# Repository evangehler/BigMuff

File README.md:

# Big Muff Pi Build

This project serves as an example guitar pedal build and some best practices for documentation / builds for UF AES Design

*(I also just really wanted a Big Muff)*

## Overview

List out how to go about this jawn

## Table of Contents
- [Hardware](#hardware)
    - [Schematic](#schematic)
    - [PCB](#pcb)
- [Simulation](#ltspice-simulation)
- [Bill of Materials](#bill-of-materials-bom)

## Project Status

| Phase                 | Status         | 
| -----                 | --------       | 
| LTSpice Simulation    | ✅             | 
| Schematic             | ✅             | 
| Component Footprints  | ✅             | 
| PCB                   | ✅              | 

## Hardware 
### Schematic:

### PCB:

## LTSpice Simulation

## Bill of Materials (BOM)

| PART                      | QTY | Part #                                 |
| ------------------------- | --- | -------------------------------------- |
| BC549 NPN Transistor      | 4   | Q1, Q2, Q3, Q4                         |
| 1N4148 Silicon Diode      | 4   | D1, D2, D3, D4                         |
| 1N5817 Schottky Diode     | 1   | D6                                     |
| 5mm LED                   | 1   | D5                                     |
| 100k Potentiometer        | 3   | RV1, RV2, RV3                          |
| 470k Resistor             | 3   | R4, R8, R14                            |
| 430k Resistor             | 1   | R19                                    |
| 100k Resistor             | 3   | R10, R13, R20                          |
| 47k Resistor              | 1   | R2                                     |
| 33k Resistor              | 2   | R1, R17                                |
| 22k Resistor              | 1   | R18                                    |
| 15k Resistor              | 1   | R21                                    |
| 10k Resistor              | 5   | R5, R7, R9, R12, R15                   |
| 4.7k Resistor             | 1   | R23                                    |
| 3.3k Resistor             | 1   | R22                                    |
| 1k Resistor               | 1   | R6                                     |
| 150 Resistor              | 2   | R11, R16                               |
| 100 Resistor              | 1   | R3                                     |
| 100uF Electrolytic Cap    | 1   | C14                                    |
| 1uF Capacitor             | 4   | C1, C3, C6, C8                         |
| 100nF Capacitor           | 5   | C4, C7, C12, C13, C15                  |
| 10nF Capacitor            | 1   | C11                                    |
| 4nF Capacitor             | 1   | C10                                    |
| 470pF Capacitor           | 3   | C2, C5, C9                             |
| Neutrik NRJ4HF 1/4" Jack  | 2   | J1, J2                                 |
| Barrel Jack w/ Switch     | 1   | J4                                     |
| 2-Pin Header (2.54mm)     | 8   | J3, J5, J6, J7, J8, J9, J10, J11       |
| M3 Mounting Hole          | 4   | H1, H2, H3, H4                         |

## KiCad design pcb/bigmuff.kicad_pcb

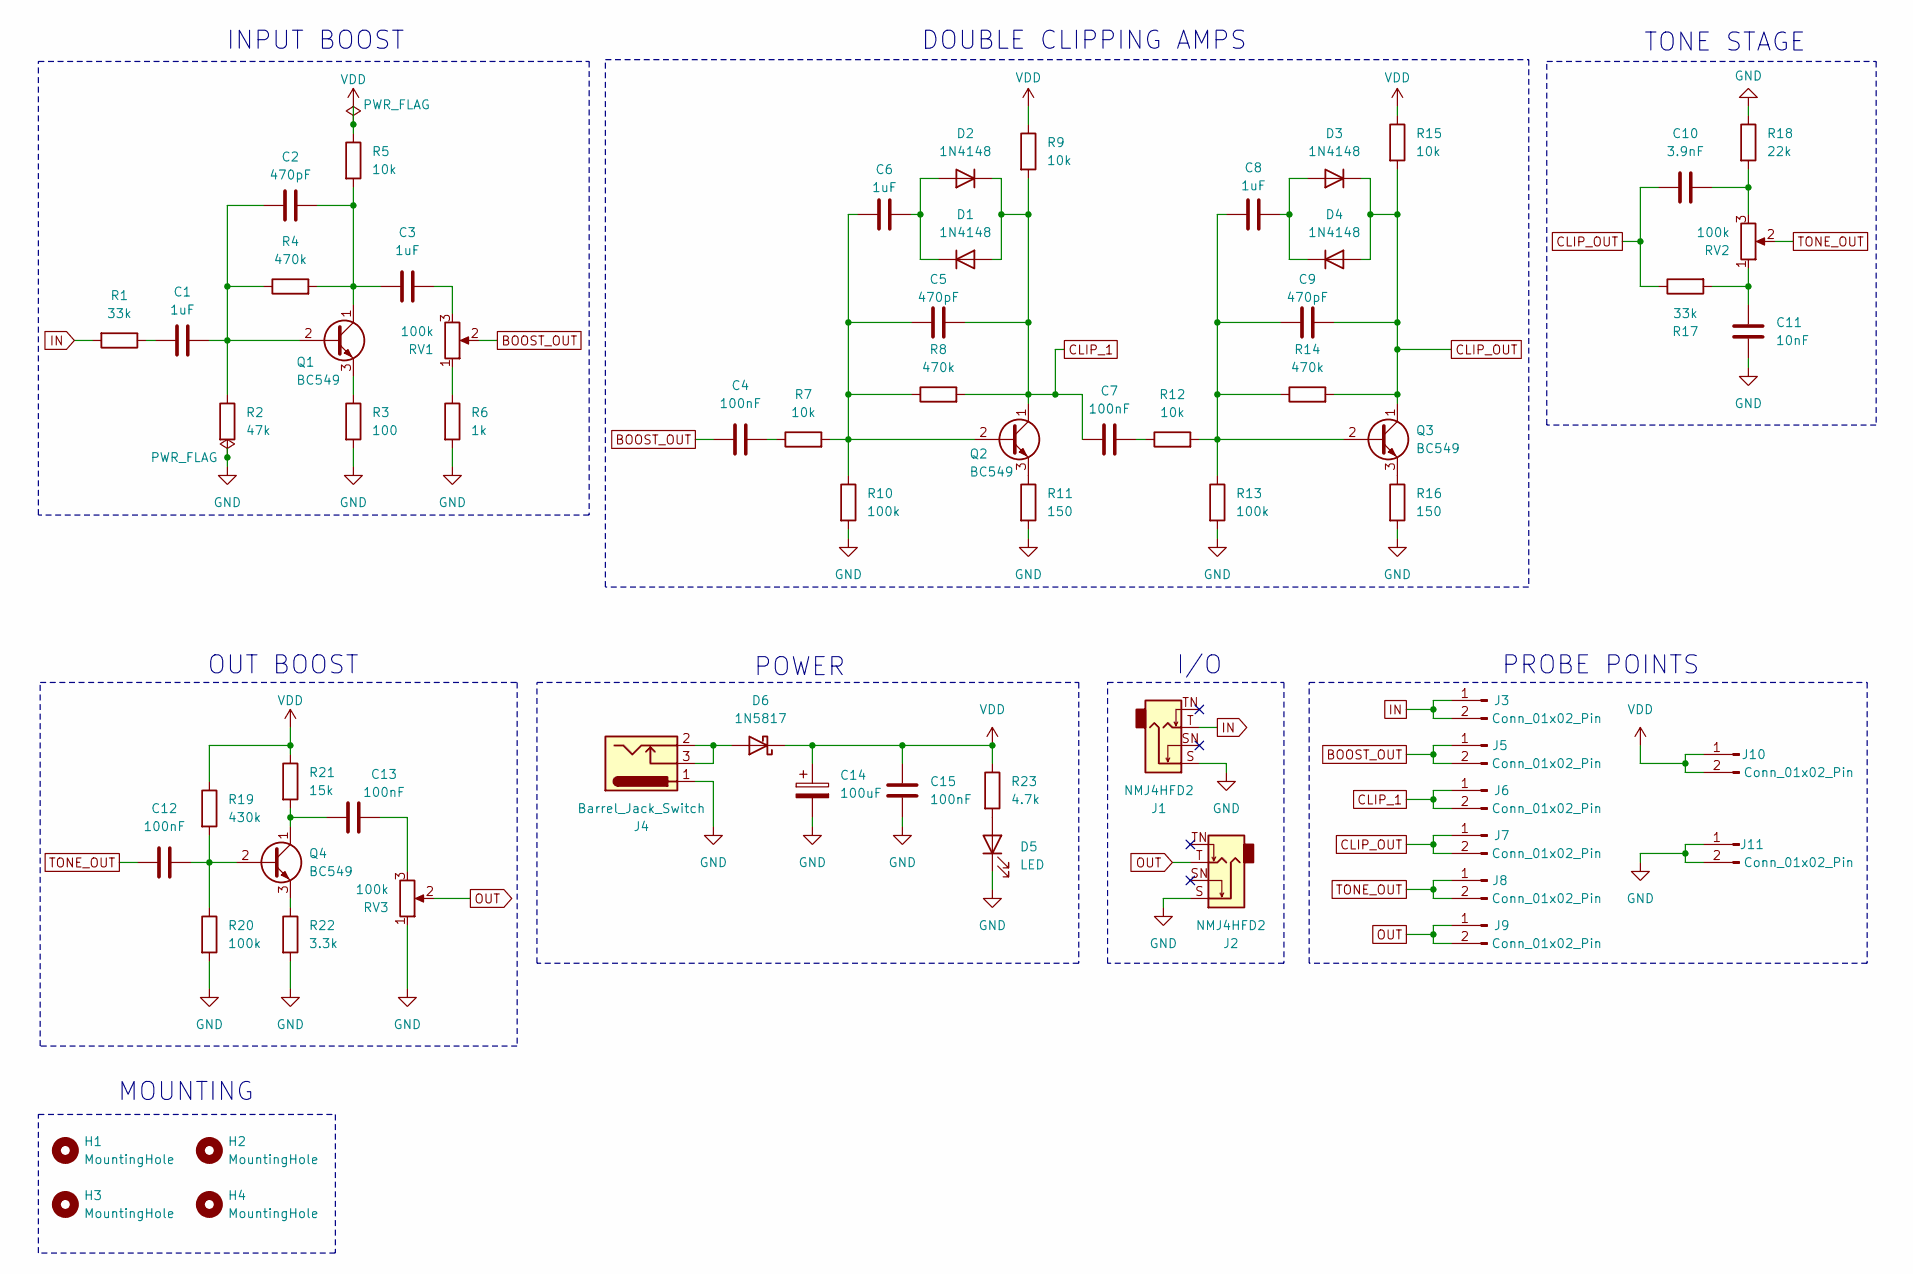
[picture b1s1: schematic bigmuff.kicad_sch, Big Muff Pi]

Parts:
C1, C3, C6, C8: 1uF; C_Rect_L7.2mm_W5.5mm_P5.00mm_FKS2_FKP2_MKS2_MKP2
C2, C5, C9: 470pF; C_Disc_D5.0mm_W2.5mm_P5.00mm
C4, C7, C12, C13: 100nF; C_Rect_L7.2mm_W2.5mm_P5.00mm_FKS2_FKP2_MKS2_MKP2
C10: 3.9nF; C_Disc_D5.0mm_W2.5mm_P5.00mm
C11: 10nF; C_Rect_L7.2mm_W2.5mm_P5.00mm_FKS2_FKP2_MKS2_MKP2
C14: 100uF; CP_Radial_D6.3mm_P2.50mm
C15: 100nF; C_Disc_D5.0mm_W2.5mm_P5.00mm
D1, D2, D3, D4: 1N4148; D_DO-35_SOD27_P7.62mm_Horizontal
D5: LED; LED_D5.0mm
D6: 1N5817; D_DO-41_SOD81_P10.16mm_Horizontal
H1, H2, H3, H4: MountingHole; MountingHole_3.2mm_M3
J1, J2: NMJ4HFD2; Jack_6.35mm_Neutrik_NMJ4HFD2_Horizontal
J3, J5, J6, J7, J8, J9, J10, J11: Conn_01x02_Pin; PinHeader_1x02_P2.54mm_Vertical
J4: Barrel_Jack_Switch; BarrelJack_Tayda_A-4118_Horizontal
Q1, Q2, Q3, Q4: BC549; TO-92_Inline_Wide
R1, R17: 33k; R_Axial_DIN0207_L6.3mm_D2.5mm_P10.16mm_Horizontal
R2: 47k; R_Axial_DIN0207_L6.3mm_D2.5mm_P10.16mm_Horizontal
R3: 100; R_Axial_DIN0207_L6.3mm_D2.5mm_P10.16mm_Horizontal
R4, R8, R14: 470k; R_Axial_DIN0207_L6.3mm_D2.5mm_P10.16mm_Horizontal
R5, R7, R9, R12, R15: 10k; R_Axial_DIN0207_L6.3mm_D2.5mm_P10.16mm_Horizontal
R6: 1k; R_Axial_DIN0207_L6.3mm_D2.5mm_P10.16mm_Horizontal
R10, R13, R20: 100k; R_Axial_DIN0207_L6.3mm_D2.5mm_P10.16mm_Horizontal
R11, R16: 150; R_Axial_DIN0207_L6.3mm_D2.5mm_P10.16mm_Horizontal
R18: 22k; R_Axial_DIN0207_L6.3mm_D2.5mm_P10.16mm_Horizontal
R19: 430k; R_Axial_DIN0207_L6.3mm_D2.5mm_P10.16mm_Horizontal
R21: 15k; R_Axial_DIN0207_L6.3mm_D2.5mm_P10.16mm_Horizontal
R22: 3.3k; R_Axial_DIN0207_L6.3mm_D2.5mm_P10.16mm_Horizontal
R23: 4.7k; R_Axial_DIN0207_L6.3mm_D2.5mm_P10.16mm_Horizontal
RV1, RV2, RV3: 100k; Potentiometer_Alpha_RD901F-40-00D_RoundLegs

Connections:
BOOST_OUT: C4.1, J5.1, J5.2, RV1.2
CLIP_1: C5.2, C7.1, D1.2 (A), D2.1 (K), J6.1, J6.2, Q2.1 (C), R8.2, R9.2
CLIP_OUT: C9.2, C10.1, D3.1 (K), D4.2 (A), J7.1, J7.2, Q3.1 (C), R14.2, R15.2, R17.1
GND: C11.1, C14.2, C15.2, D5.1 (K), J1.S, J2.S, J4.1, J11.1, J11.2, R2.2, R3.2, R6.2, R10.2, R11.2, R13.2, R16.2, R18.1, R20.2, R22.2, RV3.1
IN: J1.T, J3.1, J3.2, R1.2
unnamed: C1.2, R1.1
unnamed: C3.2, RV1.3
unnamed: C4.2, R7.1
unnamed: C7.2, R12.1
unnamed: C10.2, R18.2, RV2.3
unnamed: C11.2, R17.2, RV2.1
unnamed: C13.2, RV3.3
unnamed: C6.1, D1.1 (K), D2.2 (A)
unnamed: C8.1, D3.2 (A), D4.1 (K)
unnamed: D5.2 (A), R23.2
unnamed: D6.2 (A), J4.2, J4.3
unnamed: C1.1, C2.1, Q1.2 (B), R2.1, R4.1
unnamed: C2.2, C3.1, Q1.1 (C), R4.2, R5.2
unnamed: Q1.3 (E), R3.1
unnamed: C5.1, C6.2, Q2.2 (B), R7.2, R8.1, R10.1
unnamed: Q2.3 (E), R11.1
unnamed: C8.2, C9.1, Q3.2 (B), R12.2, R13.1, R14.1
unnamed: Q3.3 (E), R16.1
unnamed: C12.2, Q4.2 (B), R19.2, R20.1
unnamed: C13.1, Q4.1 (C), R21.2
unnamed: Q4.3 (E), R22.1
unnamed: R6.1, RV1.1
OUT: J2.T, J9.1, J9.2, RV3.2
TONE_OUT: C12.1, J8.1, J8.2, RV2.2
VDD: C14.1, C15.1, D6.1 (K), J10.1, J10.2, R5.1, R9.1, R15.1, R19.1, R21.1, R23.1

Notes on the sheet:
OUT BOOST
DOUBLE CLIPPING AMPS
I/O
PROBE POINTS
POWER
INPUT BOOST
TONE STAGE
MOUNTING

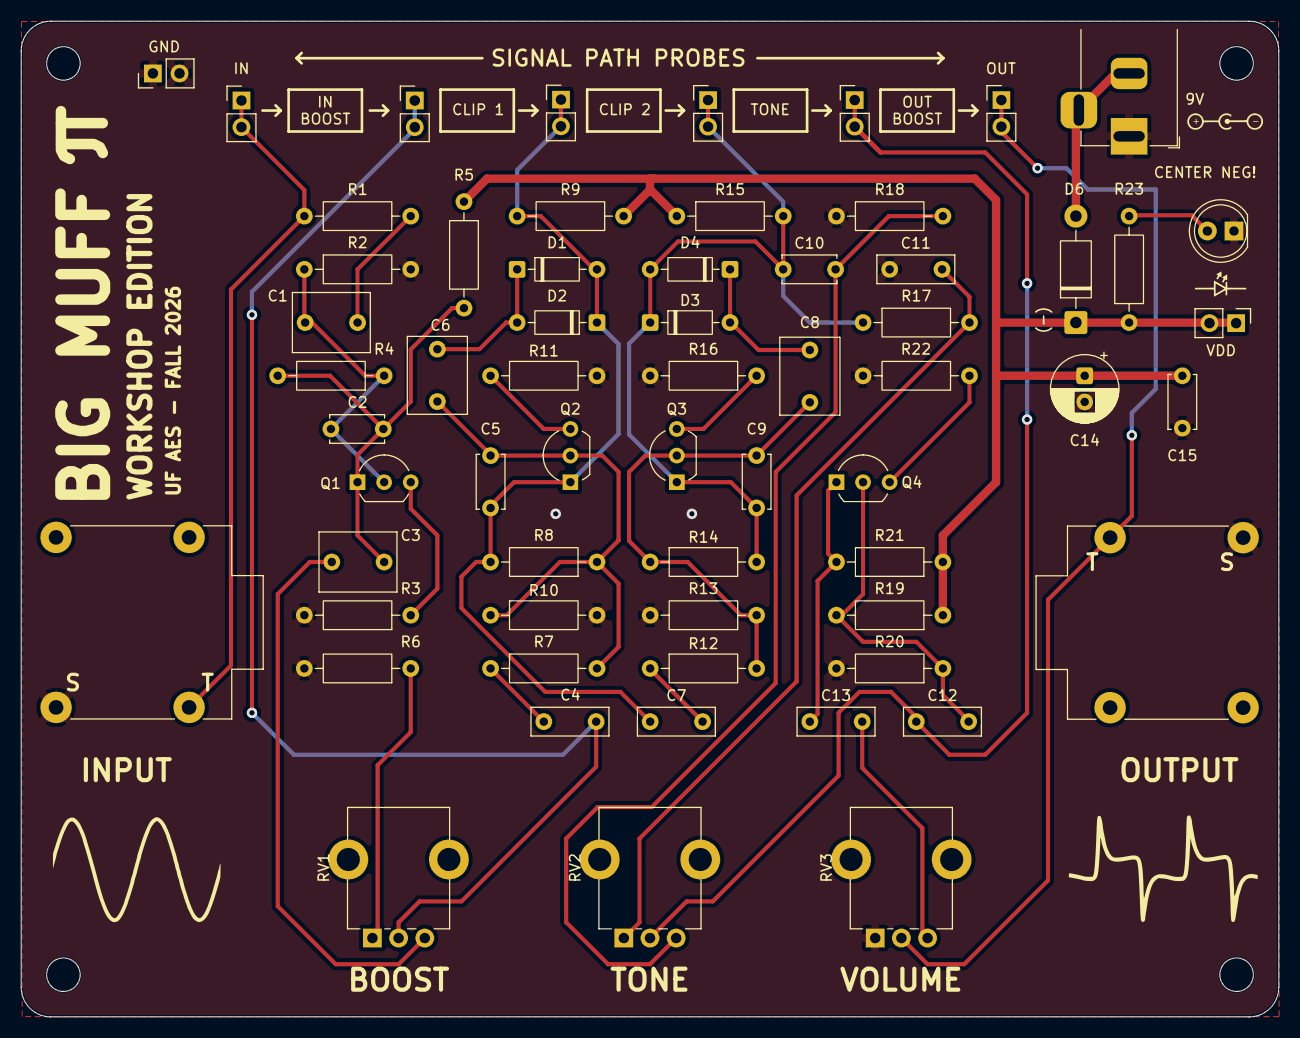
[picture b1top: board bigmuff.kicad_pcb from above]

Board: 2 copper layers, 120.1 x 95.1 mm, 66 parts (0 on the bottom side), 30 nets.

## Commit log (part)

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2026-02-05 Added LTSpice sim
2026-02-05 Added README
2026-02-05 Added .gitignore
2026-02-05 Updated readme, added schematic image
2026-02-05 reorganization
2026-02-23 Added Kicad Schematic
2026-02-23 Update Schematic, add resistor footprints
2026-02-24 Update schematic
2026-02-24 fix readme
2026-02-26 added ref
2026-03-05 Started PCB
2026-03-06 pcb progress
2026-03-06 pcb update
2026-05-25 update pcb
2026-05-25 updated pcb
2026-05-31 updated test points
2026-05-31 updated pcb, simulation, readme
2026-06-08 added 3d models
2026-06-14 Passed ERC / DRC - ready for gerbers
